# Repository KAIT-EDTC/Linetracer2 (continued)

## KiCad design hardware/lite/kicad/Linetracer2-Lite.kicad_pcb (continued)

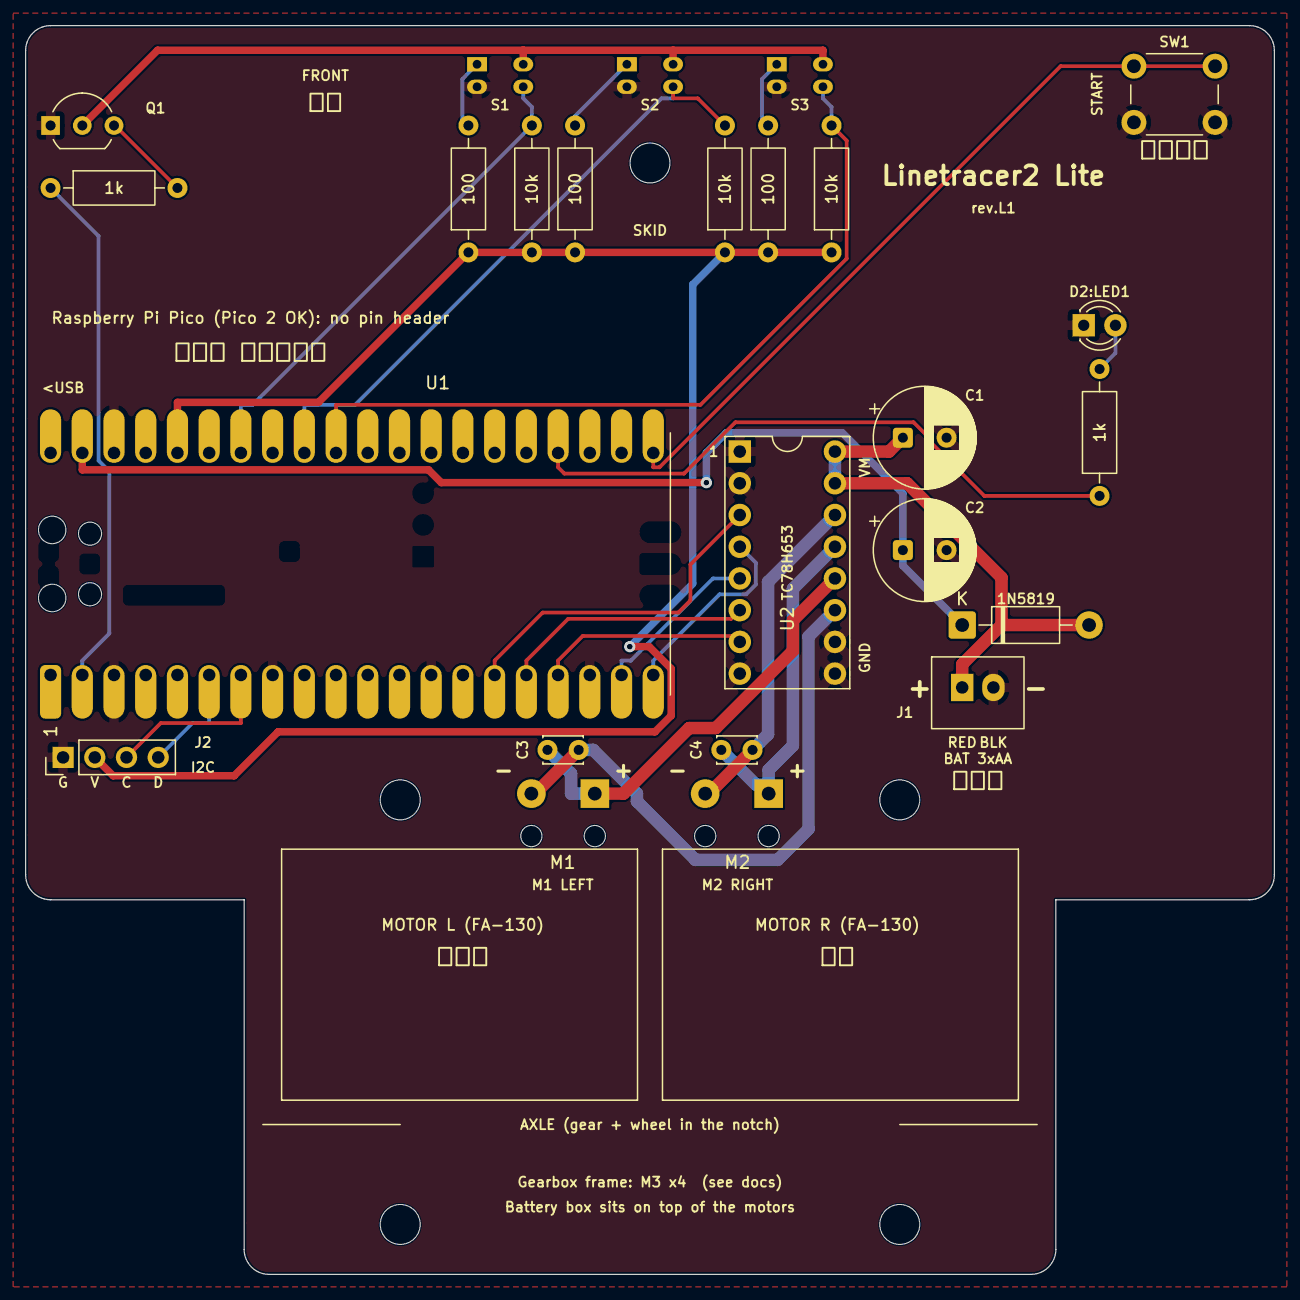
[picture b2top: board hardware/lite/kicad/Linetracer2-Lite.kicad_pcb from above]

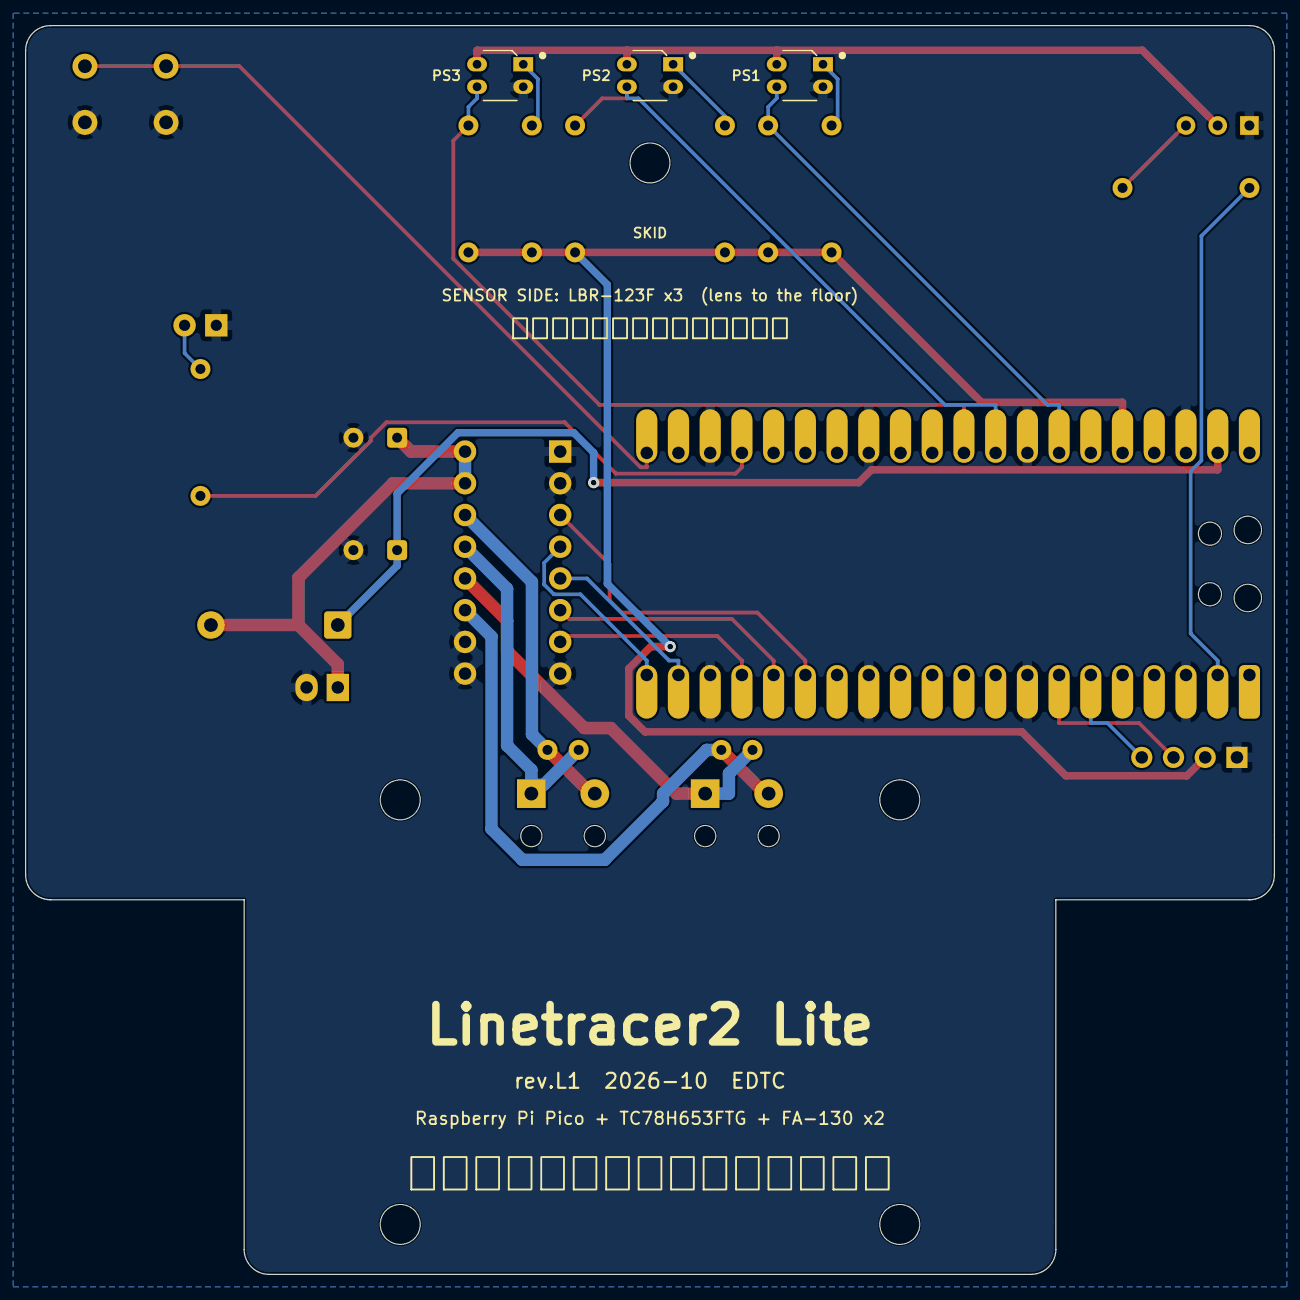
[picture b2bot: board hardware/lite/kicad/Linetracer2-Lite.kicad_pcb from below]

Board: 2 copper layers, 100.0 x 100.0 mm, 30 parts (3 on the bottom side), 27 nets.

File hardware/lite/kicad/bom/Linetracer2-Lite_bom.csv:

"Refs","Value","Footprint","Akizuki","Note","Qty"
"C1,C2","470uF 16V","Capacitor_THT:CP_Radial_D8.0mm_P3.50mm","108426 (Rubycon 16WXA470MEFC 8x9)","hold-up for Pico when motors pull the battery down,motor bulk capacitor, place near U2 VM","2"
"C3,C4","0.1uF (at motor)","Capacitor_THT:C_Disc_D3.0mm_W2.0mm_P2.50mm","113582 (10pcs)","","2"
"D1","1N5819","Diode_THT:D_DO-41_SOD81_P10.16mm_Horizontal","117244","blocks USB 5V back-feed into batteries","1"
"D2","LED red","LED_THT:LED_D3.0mm","111577","","1"
"J1","BATTERY (AA x3, XH 2P)","Linetracer2:BatteryXH_2P","112247 (B2B-XH-A) / battery box 112243","red wire = + (pin 1)","1"
"M1","LEFT motor  FA-130RA","Linetracer2:MotorPads_2P_Relief","106437","","1"
"M2","RIGHT motor FA-130RA","Linetracer2:MotorPads_2P_Relief","106437","","1"
"PS1-PS3","LBR-123F","Linetracer2:LBR-123F","116455","","3"
"Q1","2SC1815-GR","Package_TO_SOT_THT:TO-92_Inline_Wide","117089","","1"
"R1-R3","100","Resistor_THT:R_Axial_DIN0207_L6.3mm_D2.5mm_P10.16mm_Horizontal","125101 (100pcs)","","3"
"R4-R6","10k","Resistor_THT:R_Axial_DIN0207_L6.3mm_D2.5mm_P10.16mm_Horizontal","125103 (100pcs)","","3"
"R7,R8","1k","Resistor_THT:R_Axial_DIN0207_L6.3mm_D2.5mm_P10.16mm_Horizontal","125102 (100pcs)","","2"
"SW1","START","Button_Switch_THT:SW_PUSH_6mm","108075","","1"
"U1","Raspberry Pi Pico","Linetracer2:RaspberryPi_Pico_DirectSolder","116132 (Pico, Pico 2 also OK; not Pico W)","solder the castellated edge straight onto the pads, no pin header","1"
"U2","AE-TC78H653FTG","Linetracer2:AE-TC78H653FTG","114746","uses the two 1x8 pin headers that come with the module","1"

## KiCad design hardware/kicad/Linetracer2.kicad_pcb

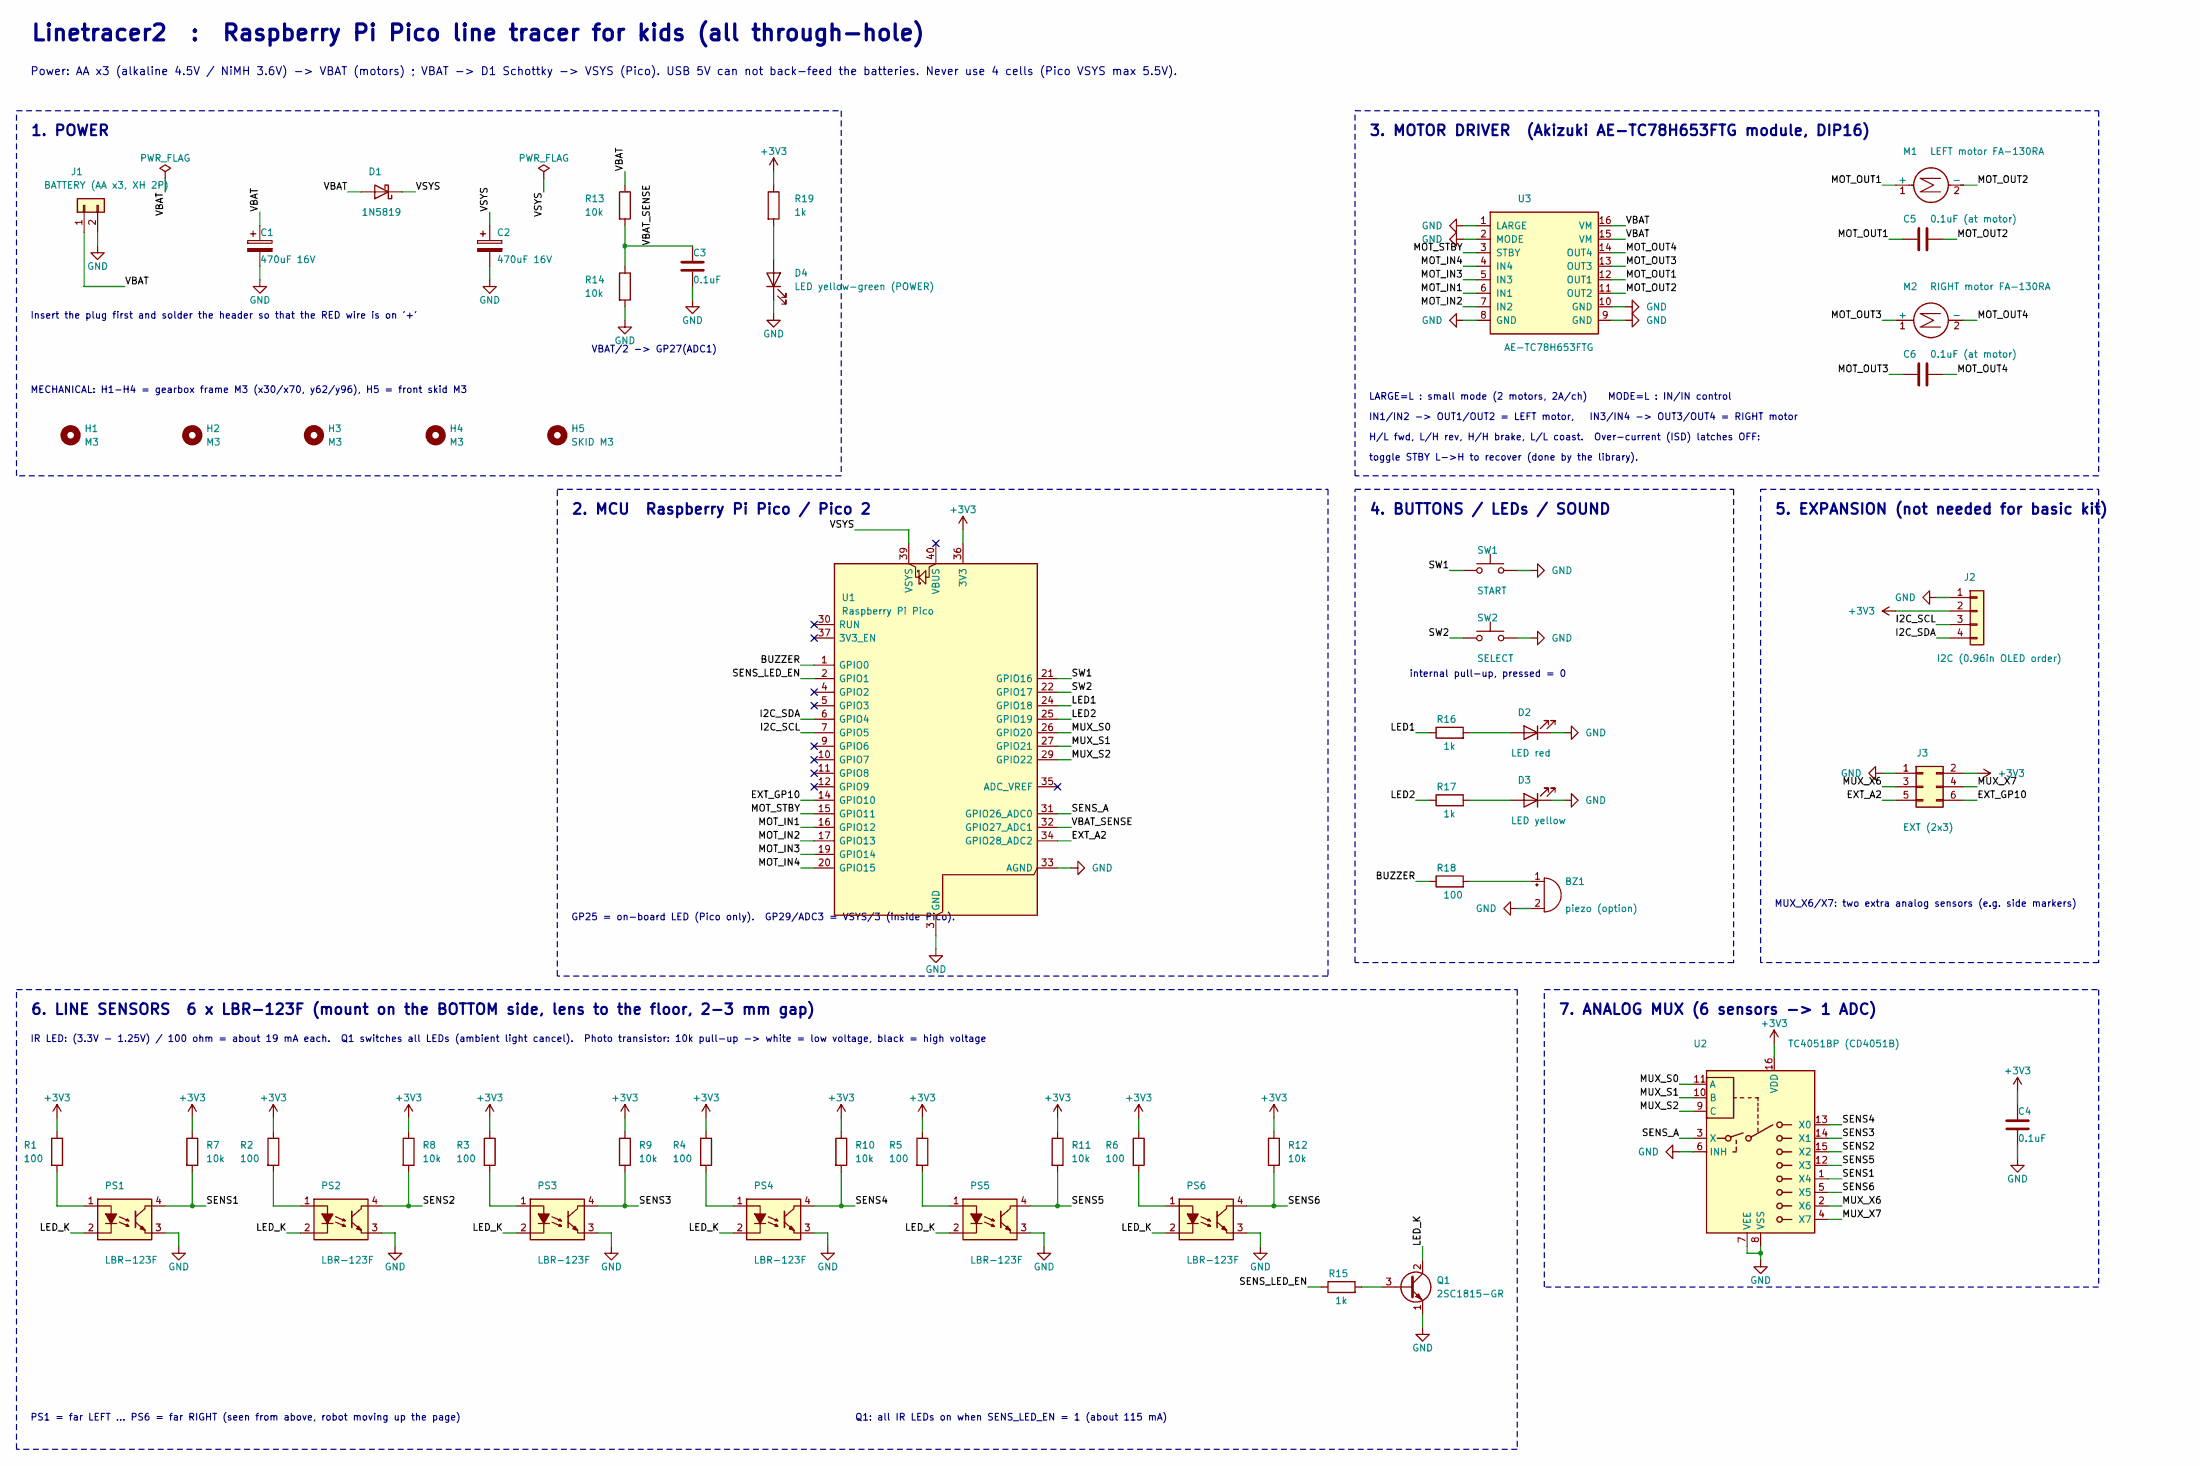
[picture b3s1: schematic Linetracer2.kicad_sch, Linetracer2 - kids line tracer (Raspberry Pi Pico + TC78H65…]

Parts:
BZ1: piezo (option); Buzzer_P5.0_P7.6
C1, C2: 470uF 16V; CP_Radial_D8.0mm_P3.50mm
C3, C4: 0.1uF; C_Disc_D3.0mm_W2.0mm_P2.50mm
C5, C6: 0.1uF (at motor); C_Disc_D3.0mm_W2.0mm_P2.50mm
D1: 1N5819; D_DO-41_SOD81_P10.16mm_Horizontal
D2: LED red; LED_D3.0mm
D3: LED yellow; LED_D3.0mm
D4: LED yellow-green (POWER); LED_D3.0mm
H1, H2, H3, H4: M3; MountingHole_3.2mm_M3
H5: SKID M3; MountingHole_3.2mm_M3
J1: BATTERY (AA x3, XH 2P); BatteryXH_2P
J2: I2C (0.96in OLED order); PinHeader_1x04_P2.54mm_Vertical
J3: EXT (2x3); PinHeader_2x03_P2.54mm_Vertical
M1: LEFT motor FA-130RA; MotorPads_2P_Relief
M2: RIGHT motor FA-130RA; MotorPads_2P_Relief
PS1, PS2, PS3, PS4, PS5, PS6: LBR-123F
Q1: 2SC1815-GR; TO-92_Inline_Wide
R1, R2, R3, R4, R5, R6, R18: 100; R_Axial_DIN0207_L6.3mm_D2.5mm_P10.16mm_Horizontal
R7, R8, R9, R10, R11, R12, R13, R14: 10k; R_Axial_DIN0207_L6.3mm_D2.5mm_P10.16mm_Horizontal
R15, R16, R17, R19: 1k; R_Axial_DIN0207_L6.3mm_D2.5mm_P10.16mm_Horizontal
SW1: START; SW_PUSH_6mm
SW2: SELECT; SW_PUSH_6mm
U1: Raspberry Pi Pico; RaspberryPi_Pico_Common_THT
U2: TC4051BP (CD4051B); DIP-16_W7.62mm
U3: AE-TC78H653FTG

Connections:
+3V3: C4.1, J2.2, J3.2, R1.1, R2.1, R3.1, R4.1, R5.1, R6.1, R7.1, R8.1, R9.1, R10.1, R11.1, R12.1, R19.1, U1.36 (3V3), U2.16 (VDD)
/BUZZER: R18.1, U1.1 (GPIO0)
/EXT_A2: J3.5, U1.34 (GPIO28_ADC2)
/EXT_GP10: J3.6, U1.14 (GPIO10)
/I2C_SCL: J2.3, U1.7 (GPIO5)
/I2C_SDA: J2.4, U1.6 (GPIO4)
/LED1: R16.1, U1.24 (GPIO18)
/LED2: R17.1, U1.25 (GPIO19)
/LED_K: PS1.2 (K), PS2.2 (K), PS3.2 (K), PS4.2 (K), PS5.2 (K), PS6.2 (K), Q1.2 (C)
/MOT_IN1: U1.16 (GPIO12), U3.6 (IN1)
/MOT_IN2: U1.17 (GPIO13), U3.7 (IN2)
/MOT_IN3: U1.19 (GPIO14), U3.5 (IN3)
/MOT_IN4: U1.20 (GPIO15), U3.4 (IN4)
/MOT_OUT1: C5.1, M1.1 (+), U3.12 (OUT1)
/MOT_OUT2: C5.2, M1.2 (-), U3.11 (OUT2)
/MOT_OUT3: C6.1, M2.1 (+), U3.13 (OUT3)
/MOT_OUT4: C6.2, M2.2 (-), U3.14 (OUT4)
/MOT_STBY: U1.15 (GPIO11), U3.3 (STBY)
/MUX_S0: U1.26 (GPIO20), U2.11 (A)
/MUX_S1: U1.27 (GPIO21), U2.10 (B)
/MUX_S2: U1.29 (GPIO22), U2.9 (C)
/MUX_X6: J3.3, U2.2 (X6)
/MUX_X7: J3.4, U2.4 (X7)
/SENS1: PS1.4 (C), R7.2, U2.1 (X4)
/SENS2: PS2.4 (C), R8.2, U2.15 (X2)
/SENS3: PS3.4 (C), R9.2, U2.14 (X1)
/SENS4: PS4.4 (C), R10.2, U2.13 (X0)
/SENS5: PS5.4 (C), R11.2, U2.12 (X3)
/SENS6: PS6.4 (C), R12.2, U2.5 (X5)
/SENS_A: U1.31 (GPIO26_ADC0), U2.3 (X)
/SENS_LED_EN: R15.1, U1.2 (GPIO1)
/SW1: SW1.1, U1.21 (GPIO16)
/SW2: SW2.1, U1.22 (GPIO17)
/VBAT: C1.1, D1.2 (A), J1.1, R13.1, U3.15 (VM), U3.16 (VM)
/VBAT_SENSE: C3.1, R13.2, R14.1, U1.32 (GPIO27_ADC1)
/VSYS: C2.1, D1.1 (K), U1.39 (VSYS)
GND: BZ1.2 (-), C1.2, C2.2, C3.2, C4.2, D2.1 (K), D3.1 (K), D4.1 (K), J1.2, J2.1, J3.1, PS1.3 (E), PS2.3 (E), PS3.3 (E), PS4.3 (E), PS5.3 (E), PS6.3 (E), Q1.1 (E), R14.2, SW1.2, SW2.2, U1.3 (GND), U1.8 (GND), U1.13 (GND), U1.18 (GND), U1.23 (GND), U1.28 (GND), U1.33 (AGND), U1.38 (GND), U2.6 (INH), U2.7 (VEE), U2.8 (VSS), U3.1 (LARGE), U3.2 (MODE), U3.8 (GND), U3.9 (GND), U3.10 (GND)
unnamed: BZ1.1 (+), R18.2
unnamed: D2.2 (A), R16.2
unnamed: D3.2 (A), R17.2
unnamed: D4.2 (A), R19.2
unnamed: PS1.1 (A), R1.2
unnamed: PS2.1 (A), R2.2
unnamed: PS3.1 (A), R3.2
unnamed: PS4.1 (A), R4.2
unnamed: PS5.1 (A), R5.2
unnamed: PS6.1 (A), R6.2
unnamed: Q1.3 (B), R15.2

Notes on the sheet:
6. LINE SENSORS 6 x LBR-123F (mount on the BOTTOM side, lens to the floor, 2-3 mm gap)
7. ANALOG MUX (6 sensors -> 1 ADC)
Power: AA x3 (alkaline 4.5V / NiMH 3.6V) -> VBAT (motors) ; VBAT -> D1 Schottky -> VSYS (Pico). USB 5V can not back-feed the batteries. Never use 4 cells (Pico VSYS max 5.5V).
GP25 = on-board LED (Pico only). GP29/ADC3 = VSYS/3 (inside Pico).
Insert the plug first and solder the header so that the RED wire is on '+'
2. MCU Raspberry Pi Pico / Pico 2
4. BUTTONS / LEDs / SOUND
1. POWER
IR LED: (3.3V - 1.25V) / 100 ohm = about 19 mA each. Q1 switches all LEDs (ambient light cancel). Photo transistor: 10k pull-up -> white = low voltage, black = high voltage
LARGE=L : small mode (2 motors, 2A/ch) MODE=L : IN/IN control
internal pull-up, pressed = 0
toggle STBY L->H to recover (done by the library).
Q1: all IR LEDs on when SENS_LED_EN = 1 (about 115 mA)
H/L fwd, L/H rev, H/H brake, L/L coast. Over-current (ISD) latches OFF:
5. EXPANSION (not needed for basic kit)
MUX_X6/X7: two extra analog sensors (e.g. side markers)
MECHANICAL: H1-H4 = gearbox frame M3 (x30/x70, y62/y96), H5 = front skid M3
VBAT/2 -> GP27(ADC1)
PS1 = far LEFT ... PS6 = far RIGHT (seen from above, robot moving up the page)
IN1/IN2 -> OUT1/OUT2 = LEFT motor, IN3/IN4 -> OUT3/OUT4 = RIGHT motor
Linetracer2 : Raspberry Pi Pico line tracer for kids (all through-hole)
3. MOTOR DRIVER (Akizuki AE-TC78H653FTG module, DIP16)

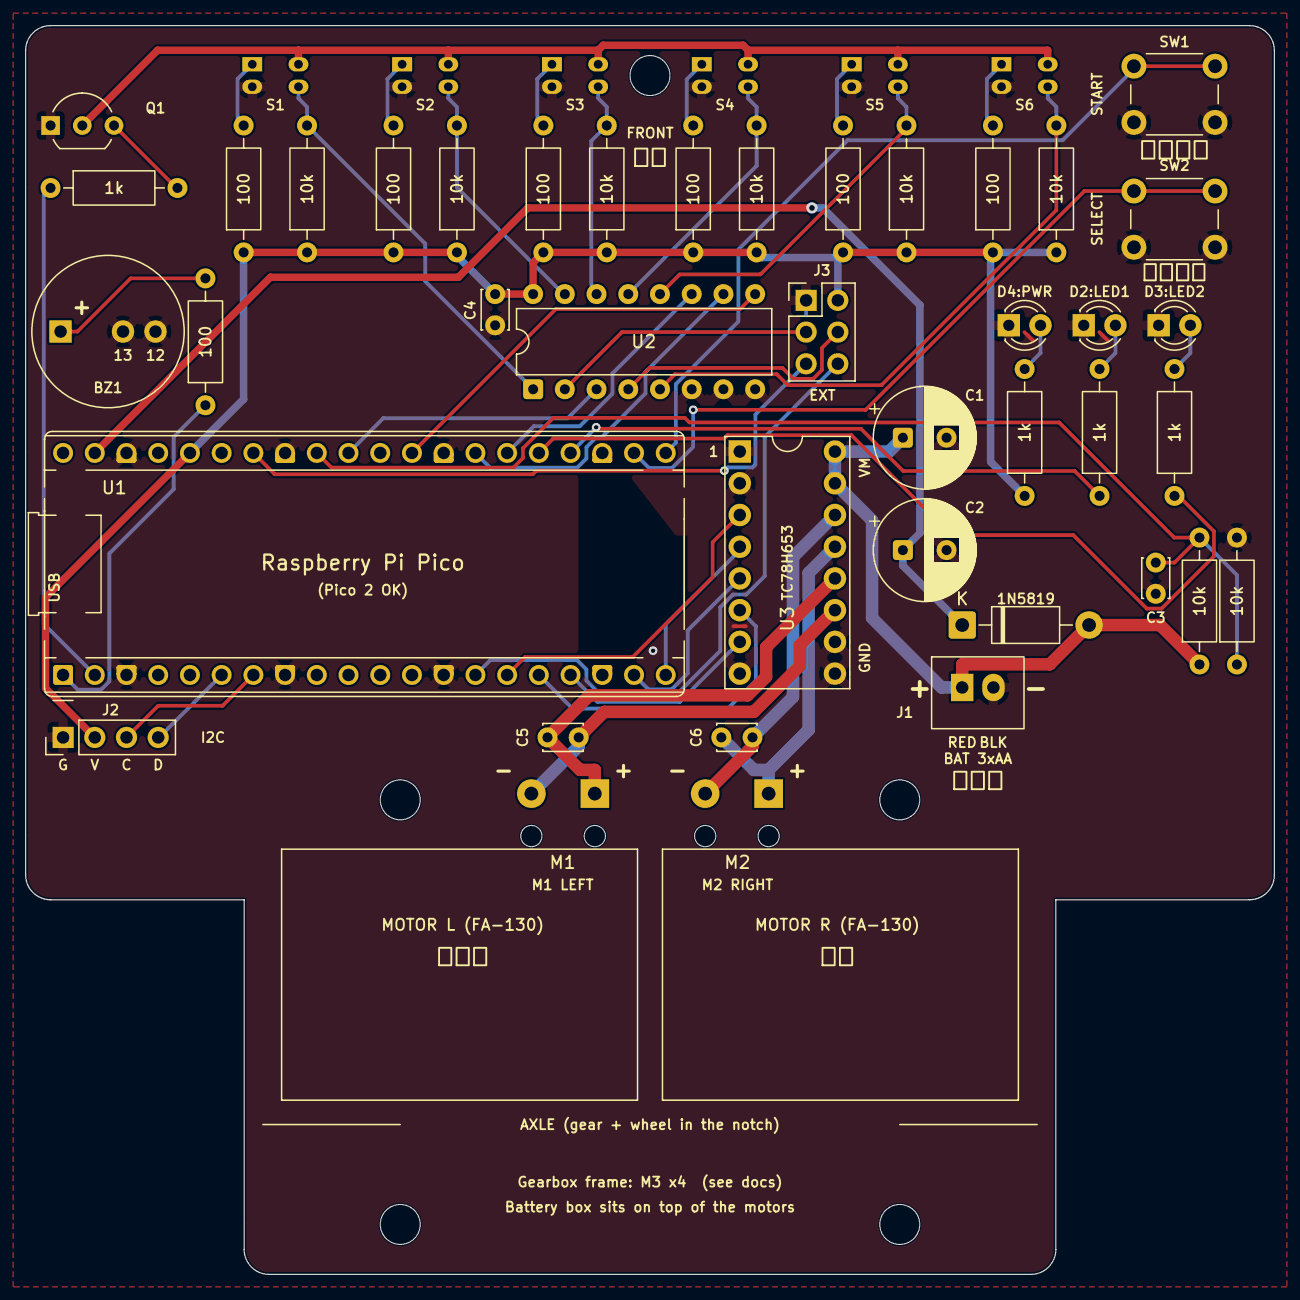
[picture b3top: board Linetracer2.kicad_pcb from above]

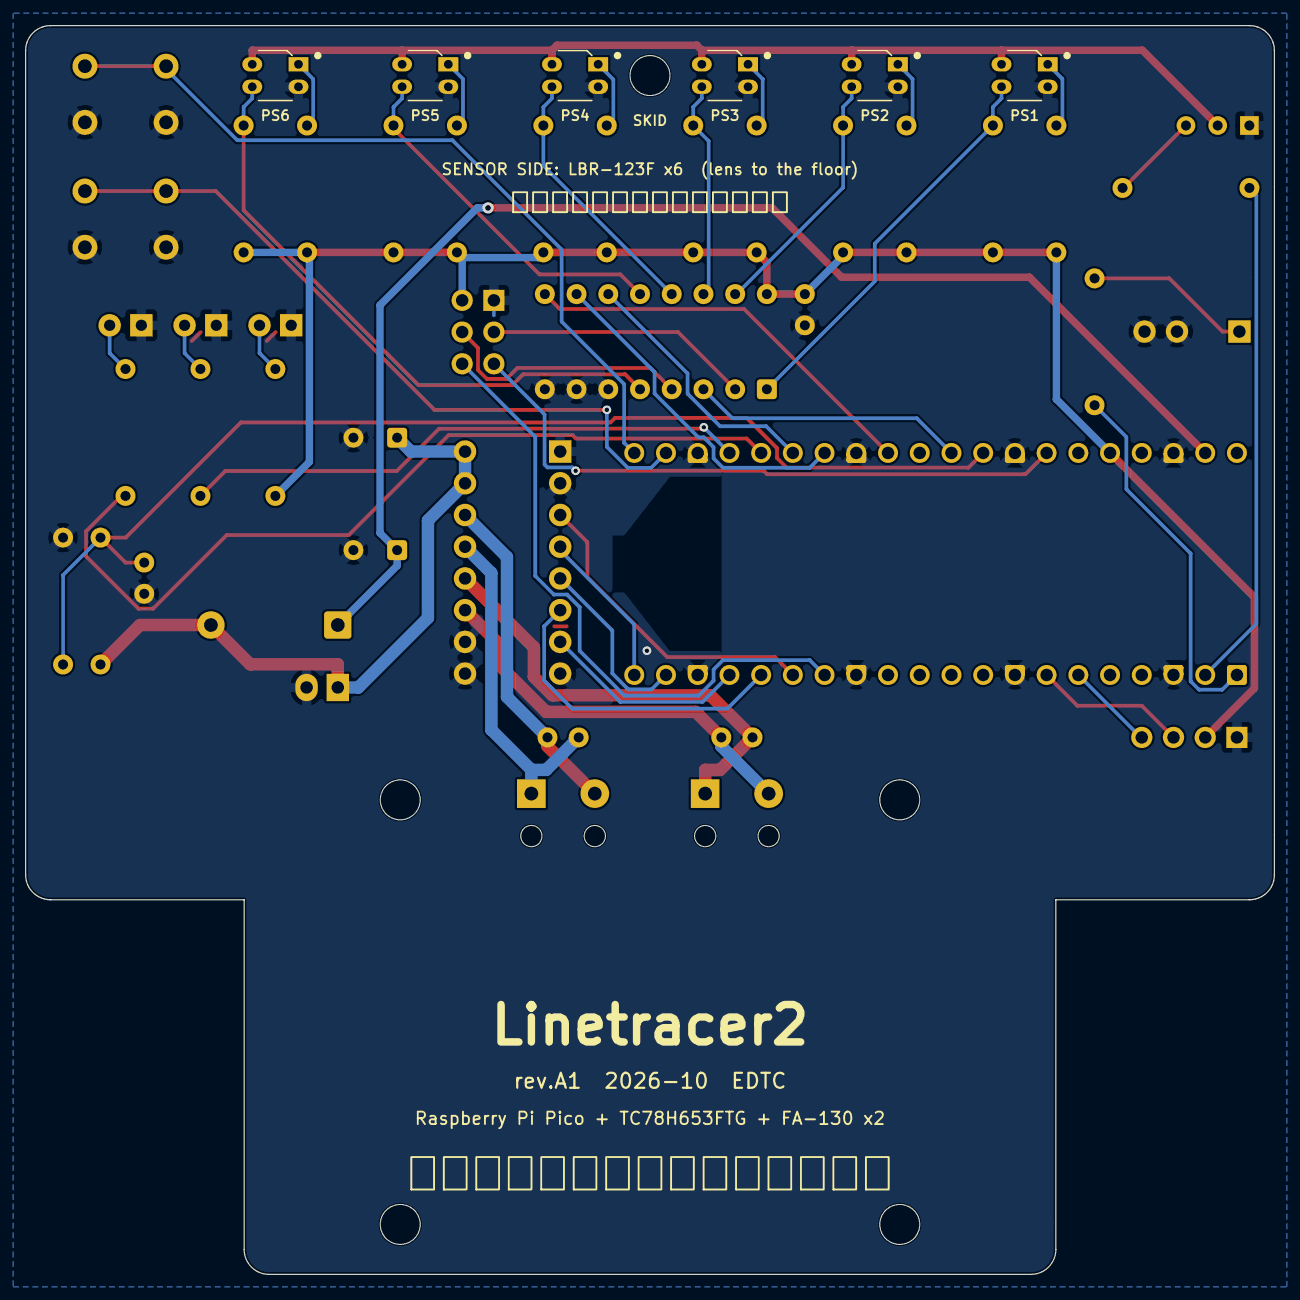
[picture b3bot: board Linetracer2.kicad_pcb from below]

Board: 2 copper layers, 100.0 x 100.0 mm, 52 parts (6 on the bottom side), 48 nets.

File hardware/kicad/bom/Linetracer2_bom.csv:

"Refs","Value","Footprint","Akizuki","Note","Qty"
"BZ1","piezo (option)","Linetracer2:Buzzer_P5.0_P7.6","104118 (PKM13EPYH4000-A0)","passive piezo, optional. 13mm PKM13EPYH4000-A0 (pitch 5.0) or 12mm (pitch 7.6)","1"
"C1,C2","470uF 16V","Capacitor_THT:CP_Radial_D8.0mm_P3.50mm","108426 (Rubycon 16WXA470MEFC 8x9)","hold-up for Pico when motors pull the battery down,motor bulk capacitor, place near U3 VM","2"
"C3,C4","0.1uF","Capacitor_THT:C_Disc_D3.0mm_W2.0mm_P2.50mm","113582 (10pcs)","","2"
"C5,C6","0.1uF (at motor)","Capacitor_THT:C_Disc_D3.0mm_W2.0mm_P2.50mm","113582 (10pcs)","","2"
"D1","1N5819","Diode_THT:D_DO-41_SOD81_P10.16mm_Horizontal","117244","blocks USB 5V back-feed into batteries","1"
"D2","LED red","LED_THT:LED_D3.0mm","111577","","1"
"D3","LED yellow","LED_THT:LED_D3.0mm","111639","","1"
"D4","LED yellow-green (POWER)","LED_THT:LED_D3.0mm","111637","","1"
"J1","BATTERY (AA x3, XH 2P)","Linetracer2:BatteryXH_2P","112247 (B2B-XH-A) / battery box 112243","red wire = + (pin 1)","1"
"J2","I2C (0.96in OLED order)","Connector_PinHeader_2.54mm:PinHeader_1x04_P2.54mm_Vertical","","","1"
"J3","EXT (2x3)","Connector_PinHeader_2.54mm:PinHeader_2x03_P2.54mm_Vertical","","","1"
"M1","LEFT motor  FA-130RA","Linetracer2:MotorPads_2P_Relief","106437","","1"
"M2","RIGHT motor FA-130RA","Linetracer2:MotorPads_2P_Relief","106437","","1"
"PS1-PS6","LBR-123F","Linetracer2:LBR-123F","116455","","6"
"Q1","2SC1815-GR","Package_TO_SOT_THT:TO-92_Inline_Wide","117089","","1"
"R1-R6,R18","100","Resistor_THT:R_Axial_DIN0207_L6.3mm_D2.5mm_P10.16mm_Horizontal","125101 (100pcs)","","7"
"R7-R14","10k","Resistor_THT:R_Axial_DIN0207_L6.3mm_D2.5mm_P10.16mm_Horizontal","125103 (100pcs)","","8"
"R15-R17,R19","1k","Resistor_THT:R_Axial_DIN0207_L6.3mm_D2.5mm_P10.16mm_Horizontal","125102 (100pcs)","","4"
"SW1","START","Button_Switch_THT:SW_PUSH_6mm","108075","","1"
"SW2","SELECT","Button_Switch_THT:SW_PUSH_6mm","108075","","1"
"U1","Raspberry Pi Pico","Module:RaspberryPi_Pico_Common_THT","116132 (Pico, Pico 2 / Pico W also OK)","","1"
"U2","TC4051BP (CD4051B)","Package_DIP:DIP-16_W7.62mm","110914","","1"
"U3","AE-TC78H653FTG","Linetracer2:AE-TC78H653FTG","114746","","1"

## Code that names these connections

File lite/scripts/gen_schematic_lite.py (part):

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    powered through its 5V pin (= USB VBUS) from a buck-boost module (rev.L4, see below)
  * 3 x LBR-127HLD sensors straight into the XIAO's three ADC pins (no 4051 multiplexer)
  * no battery measurement (the XIAO has only 3 ADC pins; all of them are used by the sensors)
  * 1 button, a passive piezo buzzer sharing the button's pin (D4), 6 full-colour LEDs (PL9823, one data line
    on D6 through R11 1k), test pads for a multimeter, no power LED, no expansion header

rev.L4 (power): the XIAO reset whenever the motors pulled hard (start, stall, 100 %): 3 x AA under 2-3 A of motor
current sag to 2.5-3.3 V, but the XIAO needs about 4 V on its 5V pin (its own Schottky + buck regulator).  Now
VBAT -> D1 -> AE-TPS63802 buck-boost (keeps running down to 1.3 V in) -> 5.13 V -> D8 -> VSYS (XIAO 5V pin,
right LED column); D8 keeps the module from feeding the PC's USB port and USB from feeding the module.
The 470 uF that sat on VSYS (= USB VBUS) is gone (USB allows 10 uF there).  The left LED column (D2 = the first
LED) runs from VSYS through D9 (1N4148, -0.7 V), so its 3.3 V data input is a valid "1" (PL9823: 0.7 x VDD).
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s.place = _place_with_code

# ----------------------------------------------------------------- headings
s.text("Linetracer2 Lite rev.L4  :  XIAO ESP32C6 on pin headers, 3 x LBR-127HLD, 1 button, 1 buzzer, 6 RGB LEDs, 5 V buck-boost", 20.32, 17.78, 3, True)
s.text("Power: AA x3 (alkaline 4.5V / NiMH 3.6V) -> VBAT (motors) ; VBAT -> D1 -> buck-boost 5.13 V -> D8 -> VSYS -> XIAO 5V pin. "
       "The XIAO no longer resets when the motors pull the cells down. Never use 4 cells (the module takes 5.5 V max).", 20.32, 24.13, 1.5)

# ================================================================= POWER block
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             fields={"Note": "reverse battery: protects U3 and the XIAO"},
             ref_off=(-2.54, -3.81), val_off=(-3.81, 3.81))
s.lab(d1, "2", "VBAT")      # A
# D1 K -> U3 VIN with EN tied to it (EN must not float: always on); one VIN_BB label names the net for the PCB
u3 = s.place("Linetracer2:AE-TPS63802", "U3", "AE-TPS63802", 104.14, 48.26, 0,
             footprint="Linetracer2:AE-TPS63802",
             fields={"Akizuki": "115557 (AE-TPS63802 kit) + 470k 125474 for VR1",
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s.wire(xk, yk, xv, yv)
s.path((xe, ye), (xe - 5.08, ye), (xe - 5.08, yv))
s.junction(xe - 5.08, yv)
s.label("VIN_BB", xk + 2.54, yk, "right")
s.power("PWR_FLAG", 83.82, 43.18, "up")
s.wire(83.82, 43.18, 83.82, yk)
s.junction(83.82, yk)
s.pwr(u3, "2", "GND")

# U3 VOUT -> D8 A (one VOUT_BB label), D8 K -> VSYS
d8 = s.place("Device:D_Schottky", "D8", "1N5819", 132.08, 45.72, 180,
             footprint="Diode_THT:D_DO-41_SOD81_P7.62mm_Horizontal",
             fields={"Note": "OR diode: U3 can not feed the PC's USB port, USB 5 V can not feed U3"},
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xo, yo, _ = u3.pin("3")
xa, ya, _ = d8.pin("2")
s.wire(xo, yo, xa, ya)
s.label("VOUT_BB", xo + 2.54, yo, "right")
xk8, yk8, _ = d8.pin("1")    # K -> VSYS, with its PWR_FLAG on the same wire
s.wire(xk8, yk8, 147.32, yk8)
s.label("VSYS", 147.32, yk8, "right")
s.power("PWR_FLAG", 142.24, 43.18, "up")
s.wire(142.24, 43.18, 142.24, yk8)
s.junction(142.24, yk8)
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s.lab(d9, "1", "VLED_L")    # K
s.power("PWR_FLAG", 198.12, 43.18, "up")
s.wire(198.12, 43.18, 198.12, 45.72)
s.label("VLED_L", 198.12, 45.72, "down")
s.text("D9: VLED_L = VSYS - 0.7 V = about 4.1 V for the left LEDs D2-D4.", 167.64, 55.88, 1.27)
s.text("A PL9823 reads '1' above 0.7 x VDD: 2.9 V there, so the XIAO's 3.3 V", 167.64, 59.69, 1.27)
s.text("data is enough.  D2-D4 pass the data on at 4.1 V, enough for D5-D7.", 167.64, 63.5, 1.27)
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                     "Note": "solder the XIAO on two 1x7 pin headers (cut from a 1x40 strip), then into the board"},
             ref_off=(-20.32, -19.05), val_off=(-20.32, -16.51))
# D0..D2 are the only ADC pins: sensors, in the order that keeps the three lines from crossing on the board.
# IN1..IN4 + button on GPIO18..23: weak pull-up only while the chip is held in reset, then floating.
# STBY on RX (GPIO17): floating during reset (-> the driver's 150k pull-down = standby), pulled up after reset
# when IN1..IN4 already float low (= coast).  Either way the motors can not start before the program runs.
# TX / RX carry the boot log and the UART REPL: only outputs there (RGB LED data, STBY), never the button.
# The XIAO's rear row (D7..D10) feeds only the motor driver behind it; everything else leaves from the front row.
# rev.L3: D3/D4 and D8/D10 swapped against rev.L2 so that no two tracks cross on the top side (see layout_lite.py).
# D4 (SW1) also drives the buzzer (through R9; the button hangs on R10).  D6 = data of the 6 RGB LEDs.
pins = {"1": "SENS3", "2": "SENS2", "3": "SENS1", "4": "SENS_LED_EN", "5": "SW1", "6": "MOT_IN2",
        "7": "RGB_DIN", "8": "MOT_STBY", "9": "MOT_IN1", "10": "MOT_IN3", "11": "MOT_IN4"}
for num, net in pins.items():
    s.lab(u1, num, net)
s.pwr(u1, "12", "+3V3")
s.pwr(u1, "13", "GND")
s.lab(u1, "14", "VSYS")
s.text("GPIO15 = yellow user LED on the XIAO (on = 0), a 2nd indicator for free.  "
       "BOOT / RESET buttons are on the XIAO.", 121.92, 171.45, 1.27)
s.text("Reset state (ESP32-C6 datasheet): GPIO18-23 weak pull-up during reset, then floating;", 121.92, 175.26, 1.27)
s.text("GPIO16 (TX) / GPIO17 (RX) pull-up after reset + boot log / UART REPL -> no button and no motor input there.",
       121.92, 179.07, 1.27)
s.text("On pin headers the XIAO sits 2.5 mm above the board: its bare bottom test pads can not touch the tracks.",
       121.92, 182.88, 1.27)
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             fields={"Akizuki": "114746", "Note": "uses the two 1x8 pin headers that come with the module"},
             ref_off=(-5.08, -13.97), val_off=(-7.62, 13.97))
# LARGE = L : small mode (2 motors, 2A/ch), MODE = L : IN/IN control.  One GND symbol for both pins: a second one
# on pin 2 would put its "GND" on top of the MOT_STBY label below it.
x1, y1, d = s.stub_end(u2, "1")
x2, y2, _ = s.stub_end(u2, "2")
s.wire(x1, y1, x2, y2)
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r10 = s.place("Device:R", "R10", "1k", 284.48, 116.84, 90, footprint=R_FP,
              ref_off=(-2.54, -2.54), val_off=(-1.27, 2.54))
s.lab(r10, "1", "SW1")
s.connect(r10, "2", sw1, "1")       # one wire with one BTN label (the PCB routes this net by name)
s.label("BTN", r10.pin("2")[0] + 1.27, r10.pin("2")[1], "right")
s.pwr(sw1, "2", "GND")
s.text("internal pull-up, pressed = 0.  R10: if START is pressed while D4 beeps, only 3.3 mA flows",
       271.78, 124.46, 1.27)
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s.connect(r9, "2", bz, "1")
s.pwr(bz, "2", "GND", length=2.54)
# beside the buzzer (below it the frame ends)
s.text("The buzzer shares D4 with the START button (no free XIAO pin).", 327.66, 176.53, 1.27)
s.text("A piezo passes no DC, so reading the button (input + pull-up)", 327.66, 180.34, 1.27)
s.text("works; to beep, D4 becomes a PWM output - it also sounds while", 327.66, 184.15, 1.27)
s.text("START is held.", 327.66, 187.96, 1.27)
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    xe, ye, _ = ps.pin("3")
    s.path((xe, ye), (xe + 2.54, ye), (xe + 2.54, ye + 2.54))
    s.power("GND", xe + 2.54, ye + 2.54, "down")
s.text("PS1 = LEFT -> D2 (GPIO2/ADC),  PS2 = CENTRE -> D1 (GPIO1/ADC),  PS3 = RIGHT -> D0 (GPIO0/ADC)  "
       "(seen from above, robot moving up the page)", 20.32, 276.86, 1.27)

# LED switch
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
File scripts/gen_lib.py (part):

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def sym_xiao():
    """Seeed Studio XIAO ESP32C6 (14 castellated pins). Drawn like the board seen from above with the USB up:
    left 1..7 = D0..D6, right 14..8 = 5V, GND, 3V3, D10..D7.  Names: GPIO number / XIAO name."""
    left = [("1", "GPIO0/A0/D0"), ("2", "GPIO1/A1/D1"), ("3", "GPIO2/A2/D2"), ("4", "GPIO21/D3"),
            ("5", "GPIO22/SDA/D4"), ("6", "GPIO23/SCL/D5"), ("7", "GPIO16/TX/D6")]
    right = [("14", "5V", "power_in"), ("13", "GND", "power_in"), ("12", "3V3", "power_out"),
             ("11", "GPIO18/MOSI/D10", "bidirectional"), ("10", "GPIO20/MISO/D9", "bidirectional"),
             ("9", "GPIO19/SCK/D8", "bidirectional"), ("8", "GPIO17/RX/D7", "bidirectional")]
    ys = [7.62, 5.08, 2.54, 0, -2.54, -5.08, -7.62]
    pins = [pin("bidirectional", -22.86, y, 0, n, num) for (num, n), y in zip(left, ys)]
    pins += [pin(k, 22.86, y, 180, n, num) for (num, n, k), y in zip(right, ys)]
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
